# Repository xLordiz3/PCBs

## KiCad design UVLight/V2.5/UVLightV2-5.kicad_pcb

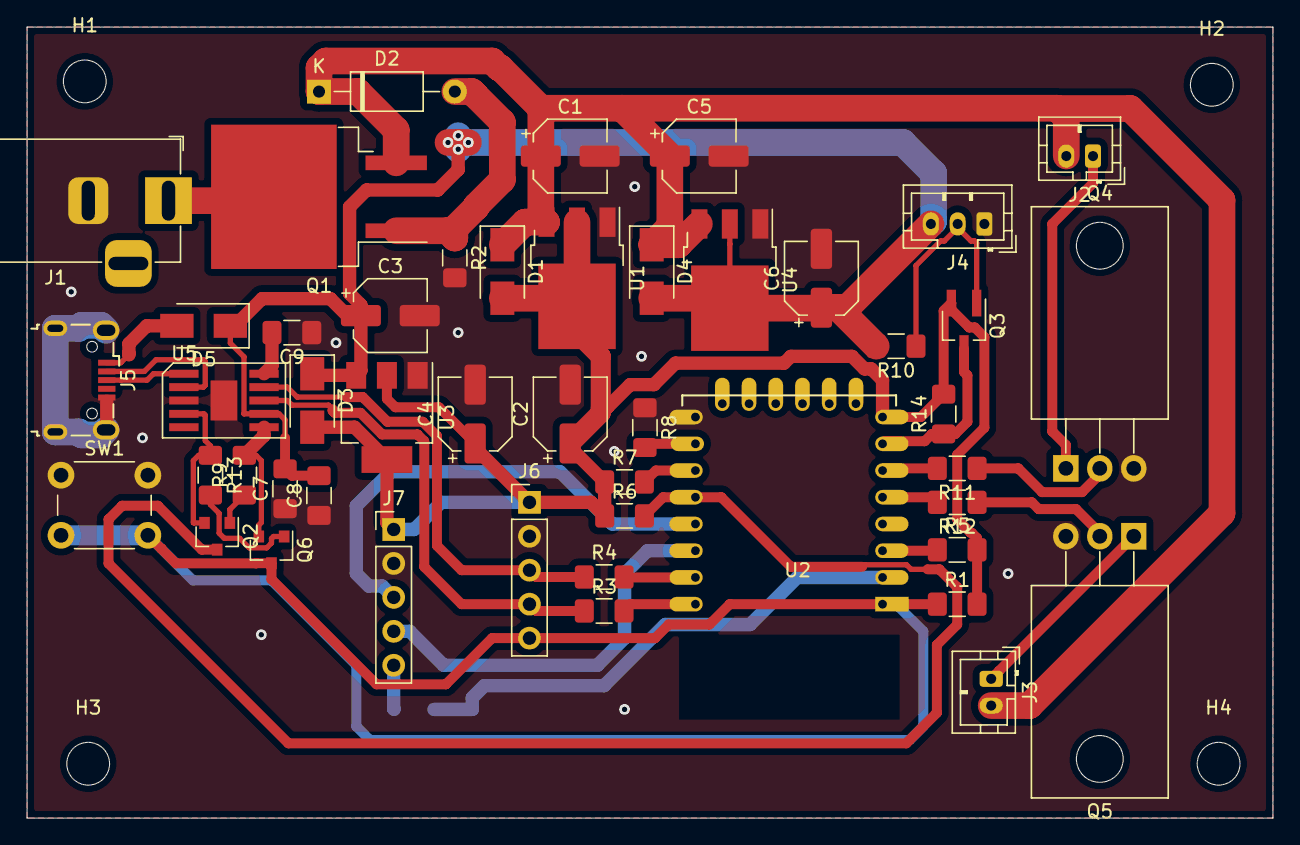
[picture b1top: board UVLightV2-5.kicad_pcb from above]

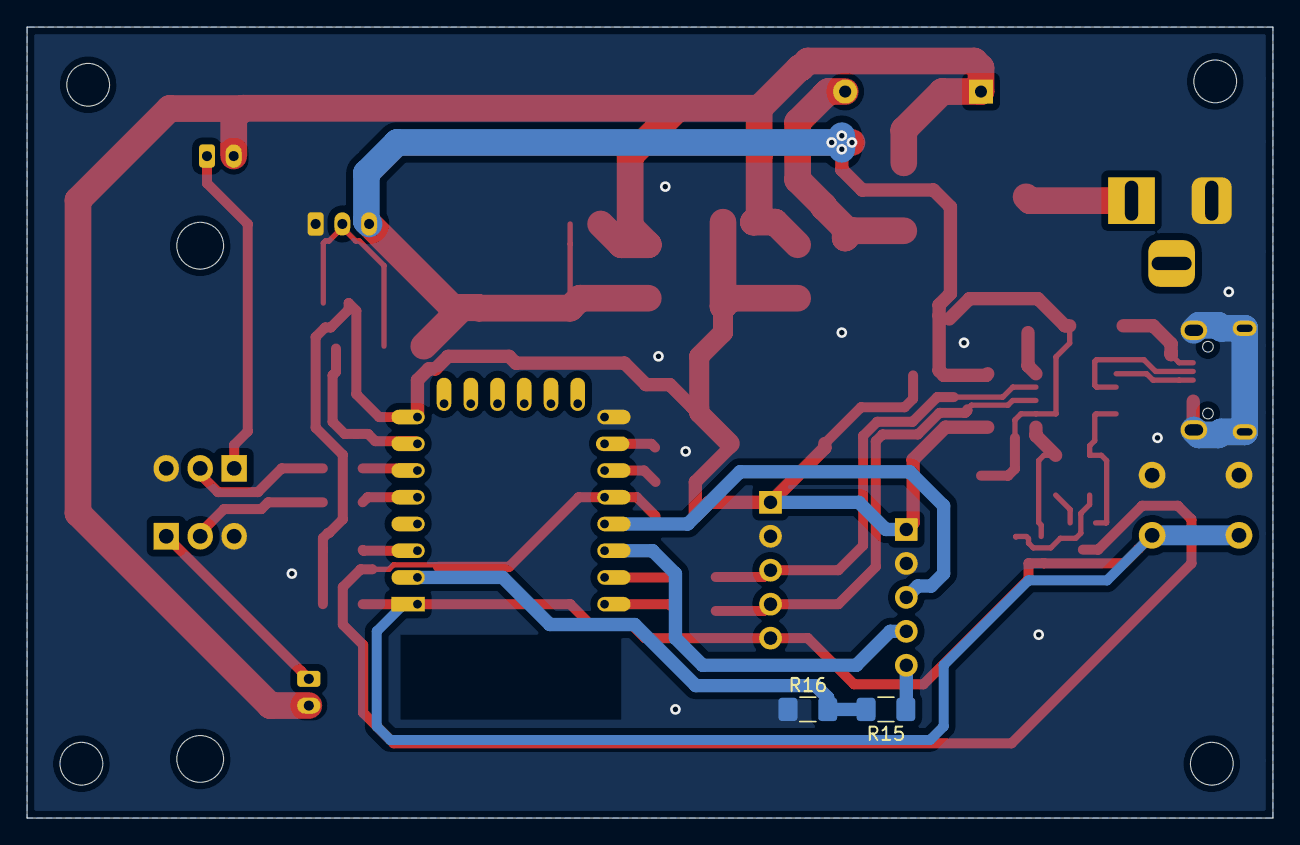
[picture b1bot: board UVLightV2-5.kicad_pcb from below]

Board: 2 copper layers, 93.2 x 59.2 mm, 53 parts (2 on the bottom side), 35 nets.

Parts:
C1, C2, C3, C4, C5, C6: C 10uF; CP_Elec_5x5.4
C7: C 10uF; C_1206_3216Metric_Pad1.42x1.75mm_HandSolder
C8, C9: C 100nF; C_1206_3216Metric_Pad1.42x1.75mm_HandSolder
D1, D3, D4, D5: 1N4002; D_SMA
D2: Z 9.1V; D_A-405_P10.16mm_Horizontal
H1, H2, H3, H4: MountingHole; MountingHole_3.2mm_M3
J1: Barrel_Jack_MountingPin; BarrelJack_Horizontal
J2: 24V LED Out; JST_PH_B2B-PH-K_1x02_P2.00mm_Vertical
J3: 24V Fan Out; JST_PH_B2B-PH-K_1x02_P2.00mm_Vertical
J4: 5V RGB Out; JST_PH_B3B-PH-K_1x03_P2.00mm_Vertical
J5: USB_B_Micro; USB_Micro-B_Wuerth_629105150521
J6: Alt Program; PinHeader_1x05_P2.54mm_Vertical
J7: Out IO; PinHeader_1x05_P2.54mm_Vertical
Q1: FQB47P06; TO-263-2
Q2, Q6: S8050; SOT-23
Q3: BS170; SOT-23W_Handsoldering
Q4, Q5: FQP30N06L; TO-220-3_Horizontal_TabDown
R1, R5, R6, R7, R8, R9, R13: R 10K; R_1206_3216Metric_Pad1.42x1.75mm_HandSolder
R2, R11, R12: R; R_1206_3216Metric_Pad1.42x1.75mm_HandSolder
R3, R4: R 470; R_1206_3216Metric_Pad1.42x1.75mm_HandSolder
R10, R14: R 4.7K; R_1206_3216Metric_Pad1.42x1.75mm_HandSolder
R15: R 220K; R_1206_3216Metric_Pad1.42x1.75mm_HandSolder
R16: R 100K; R_1206_3216Metric_Pad1.42x1.75mm_HandSolder
SW1: SW_Push; SW_PUSH_6mm
U1: IFX27001TFV33ATMA1; TO-252-3_TabPin2
U2: ESP-12E
U3: LM1117-3.3; SOT-223-3_TabPin2
U4: IFX27001TFV50ATMA1; TO-252-3_TabPin2
U5: ch340k; ESSOP-10

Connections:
+3.3VA: C2.1, C4.1, D1.2, D3.2, J6.1, J7.1, Q3.2, R1.2, R5.2, R6.1, R7.1, R14.2, U1.2, U2.8, U3.2
+5V: C3.1, C6.1, C7.2, C8.2, D3.1, D4.2, D5.1, J4.3, R10.2, U3.3, U4.2, U5.7
+24V: C1.1, C5.1, D1.1, D2.1, D4.1, J2.2, J3.2, Q1.3, U1.3, U4.3
/ADC: R15.2, R16.2, U2.2
/DTR: Q2.2, R13.1, U5.4
/Fan: R12.2, U2.5
/IO0: Q2.3, R6.2, U2.12
/IO4: J7.3, U2.13
/IO5: J7.4, U2.14
/RGB: Q3.3, R14.1, U2.7
/RST: J6.5, Q6.3, R1.1, SW1.2, U2.1
/RTS: Q6.2, R9.2, U5.6
/RX: J6.3, R4.1, U5.9
/TX: J6.4, R3.1, U5.8
/White: R11.2, U2.6
GND: C1.2, C2.2, C3.2, C4.2, C5.2, C6.2, C7.1, C8.1, C9.1, J1.2, J4.1, J5.5, J5.6, J6.2, J7.2, Q4.3, Q5.3, R2.2, R8.1, R16.1, SW1.1, U1.1, U2.9, U3.1, U4.1, U5.0, U5.3
unnamed: C9.2, U5.10
unnamed: D2.2, Q1.1, R2.1
unnamed: D5.2, J5.1
unnamed: J1.1, Q1.2
unnamed: J2.1, Q4.1
unnamed: J3.1, Q5.1
unnamed: J4.2, Q3.1, R10.1
unnamed: J5.2, U5.2
unnamed: J5.3, U5.1
unnamed: J7.5, R15.1
unnamed: Q2.1, R9.1
unnamed: Q4.2, R11.1
unnamed: Q5.2, R12.1
unnamed: Q6.1, R13.2
unnamed: R3.2, U2.16
unnamed: R4.2, U2.15
unnamed: R5.1, U2.3
unnamed: R7.2, U2.11
unnamed: R8.2, U2.10

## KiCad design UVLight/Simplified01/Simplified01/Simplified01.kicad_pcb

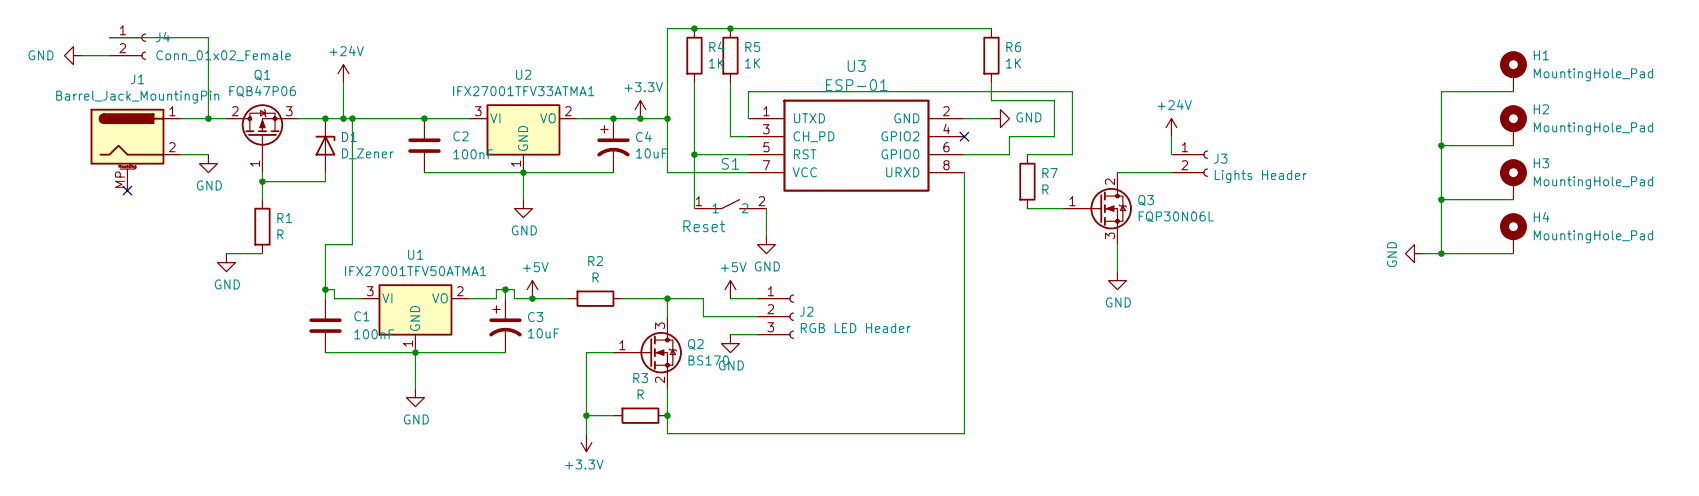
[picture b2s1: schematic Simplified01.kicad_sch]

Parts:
C1, C2: 100nF; C_1206_3216Metric_Pad1.33x1.80mm_HandSolder
C3, C4: 10uF; CP_Elec_5x5.4
D1: D_Zener; D_SOD-123F
H1, H2, H3, H4: MountingHole_Pad; MountingHole_2.2mm_M2_Pad
J1: Barrel_Jack_MountingPin; BarrelJack_Horizontal
J2: RGB LED Header; JST_XH_B3B-XH-A_1x03_P2.50mm_Vertical
J3: Lights Header; JST_XH_B2B-XH-A_1x02_P2.50mm_Vertical
J4: Conn_01x02_Female; JST_XH_B2B-XH-A_1x02_P2.50mm_Vertical
Q1: FQB47P06; TO-252-2
Q2: BS170; SOT-23
Q3: FQP30N06L; TO-220-3_Vertical
R1, R2, R3, R7: R; R_1206_3216Metric_Pad1.30x1.75mm_HandSolder
R4, R5, R6: 1K; R_1206_3216Metric_Pad1.30x1.75mm_HandSolder
S1: Reset; SW_SPST_EVQPE1
U1: IFX27001TFV50ATMA1; TO-252-3_TabPin2
U2: IFX27001TFV33ATMA1; TO-252-3_TabPin2
U3: ESP-01

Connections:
+3V3: C4.1, Q2.1 (G), R3.2, R4.1, R5.1, R6.1, U2.2 (VO), U3.7 (VCC)
+5V: C3.1, J2.1, R2.2, U1.2 (VO)
+24V: C1.1, C2.1, D1.1 (K), J3.1, Q1.3 (S), U1.3 (VI), U2.3 (VI)
GND: C1.2, C2.2, C3.2, C4.2, H1.1, H2.1, H3.1, H4.1, J1.2, J2.3, J4.2, Q3.3 (S), R1.2, S1.2, U1.1 (GND), U2.1 (GND), U3.2 (GND)
unnamed: D1.2 (A), Q1.1 (G), R1.1
unnamed: J1.1, J4.1, Q1.2 (D)
unnamed: J2.2, Q2.3 (D), R2.1
unnamed: J3.2, Q3.2 (D)
unnamed: Q2.2 (S), R3.1, U3.8 (URXD)
unnamed: Q3.1 (G), R7.2
unnamed: R4.2, S1.1, U3.5 (RST)
unnamed: R5.2, U3.3 (CH_PD)
unnamed: R6.2, U3.6 (GPIO0)
unnamed: R7.1, U3.1 (UTXD)

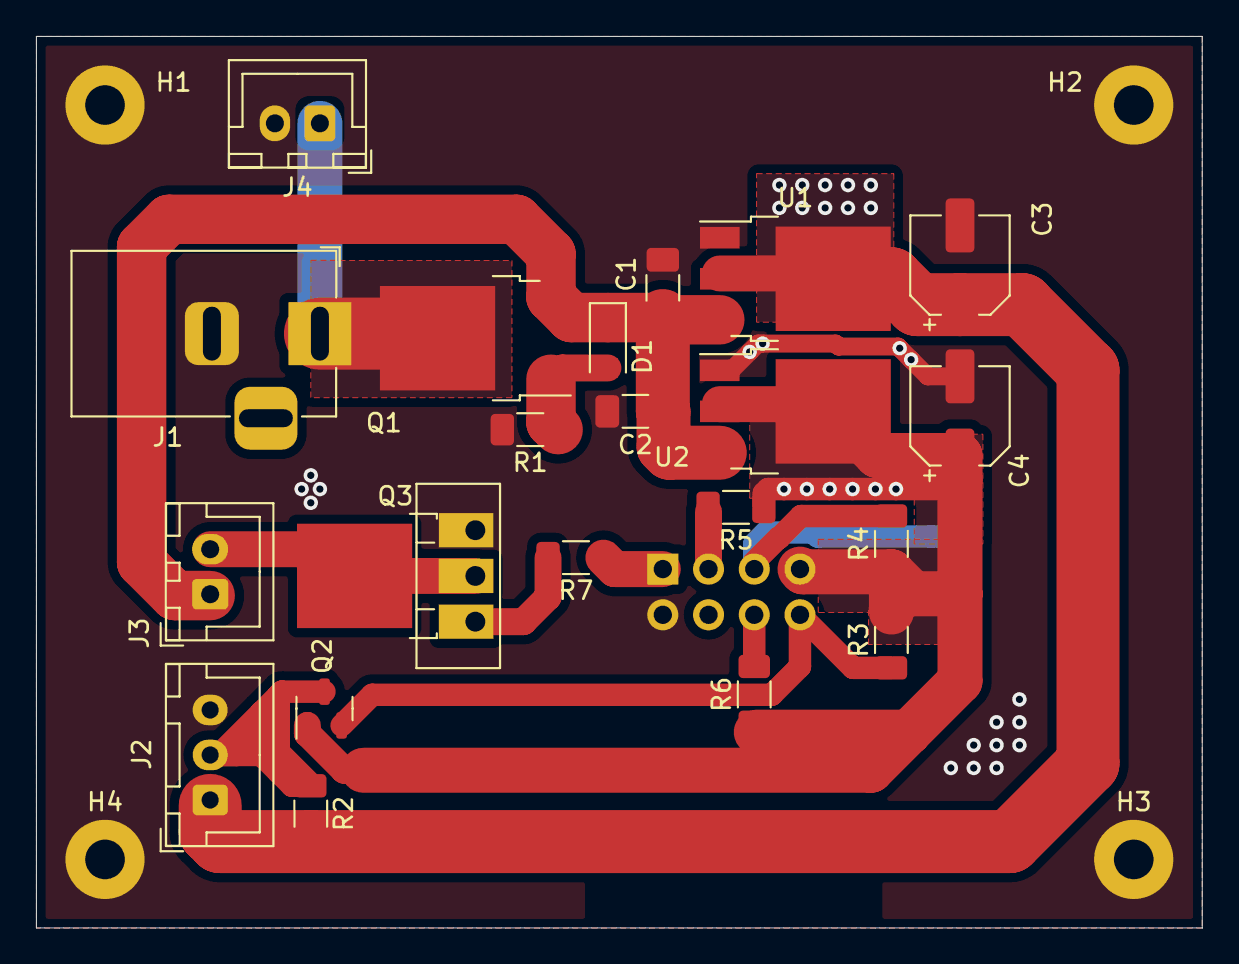
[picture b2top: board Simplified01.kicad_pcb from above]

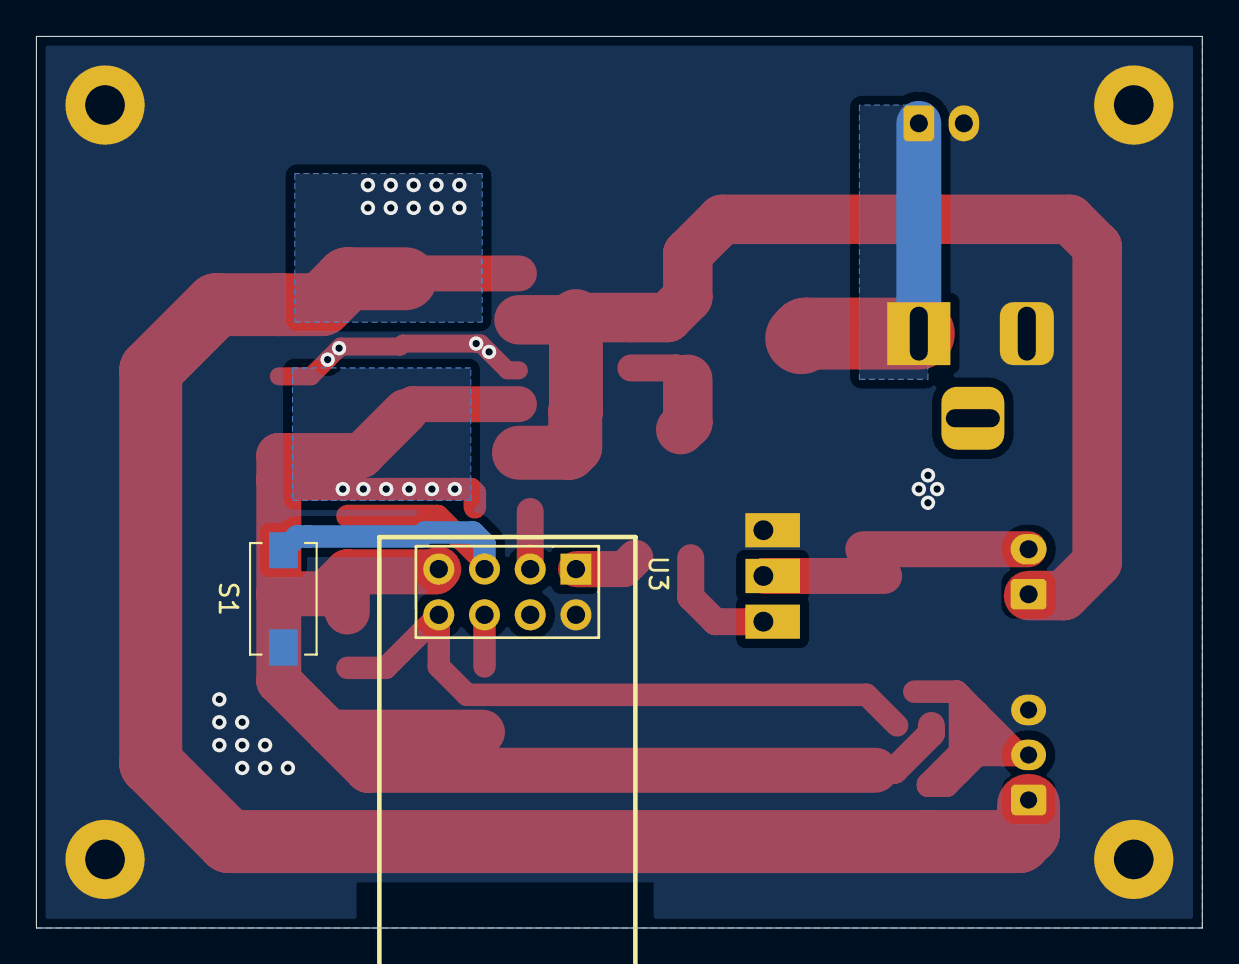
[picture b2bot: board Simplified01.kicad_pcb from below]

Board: 2 copper layers, 64.8 x 49.5 mm, 27 parts (2 on the bottom side), 14 nets.

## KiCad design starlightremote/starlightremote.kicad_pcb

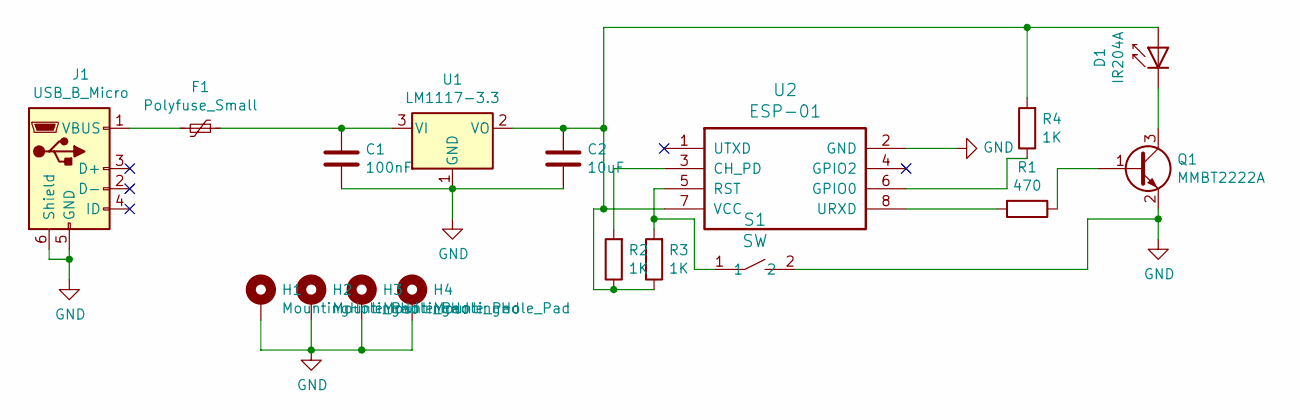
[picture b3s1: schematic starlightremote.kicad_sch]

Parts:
C1: 100nF; C_1206_3216Metric_Pad1.33x1.80mm_HandSolder
C2: 10uF; CP_Elec_5x5.4
D1: IR204A; LED_D3.0mm_IRBlack
F1: Polyfuse_Small; Fuse_0805_2012Metric_Pad1.15x1.40mm_HandSolder
H1, H2, H3, H4: MountingHole_Pad; MountingHole_2.2mm_M2_Pad
J1: USB_B_Micro; USB_Micro-B_Wuerth_629105150521
Q1: MMBT2222A; SOT-23
R1: 470; R_1206_3216Metric_Pad1.30x1.75mm_HandSolder
R2, R3, R4: 1K; R_1206_3216Metric_Pad1.30x1.75mm_HandSolder
S1: SW; SW_SPST_CK_RS282G05A3
U1: LM1117-3.3; SOT-223-3_TabPin2
U2: ESP-01

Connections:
GND: C1.2, C2.2, H1.1, H2.1, H3.1, H4.1, J1.5 (GND), J1.6 (Shield), Q1.2 (E), S1.2, U1.1 (GND), U2.2 (GND)
unnamed: C1.1, F1.1, U1.3 (VI)
unnamed: C2.1, D1.2 (A), R2.1, R3.1, R4.2, U1.2 (VO), U2.7 (VCC)
unnamed: D1.1 (K), Q1.3 (C)
unnamed: F1.2, J1.1 (VBUS)
unnamed: Q1.1 (B), R1.1
unnamed: R1.2, U2.8 (URXD)
unnamed: R2.2, U2.3 (CH_PD)
unnamed: R3.2, S1.1, U2.5 (RST)
unnamed: R4.1, U2.6 (GPIO0)

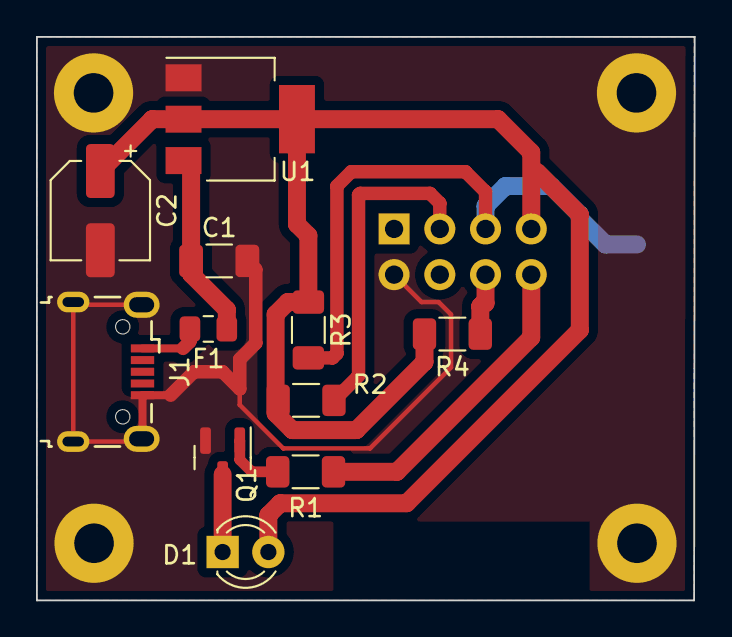
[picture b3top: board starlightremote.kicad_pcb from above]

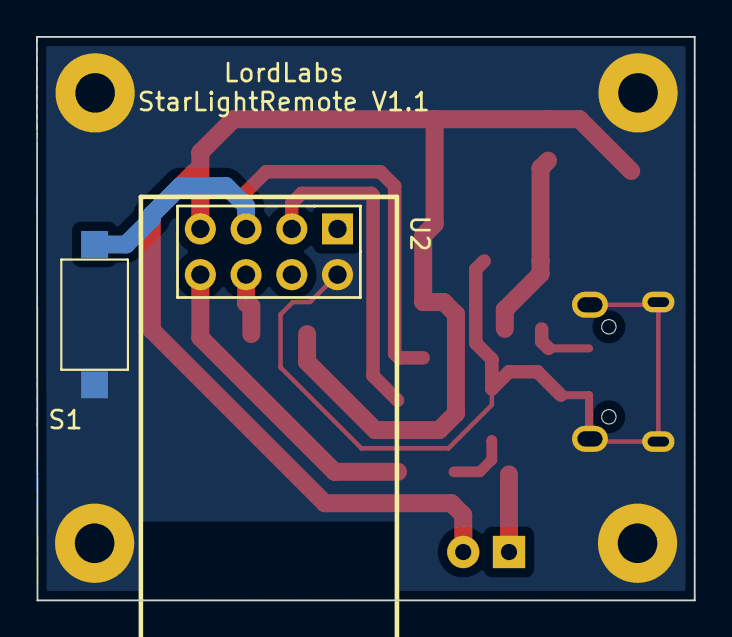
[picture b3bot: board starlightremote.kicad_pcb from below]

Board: 2 copper layers, 36.5 x 31.3 mm, 17 parts (2 on the bottom side), 10 nets.

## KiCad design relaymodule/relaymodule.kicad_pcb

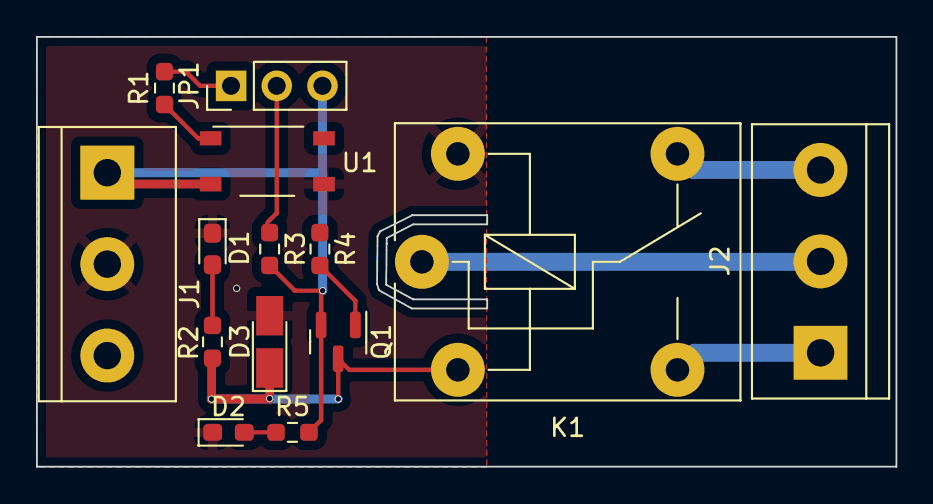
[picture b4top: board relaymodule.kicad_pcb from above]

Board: 2 copper layers, 47.8 x 23.9 mm, 14 parts (0 on the bottom side), 12 nets.

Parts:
D1, D2: LED; LED_0603_1608Metric_Pad1.05x0.95mm_HandSolder
D3: D; D_MicroMELF_Handsoldering
J1: Inputs; TerminalBlock_bornier-3_P5.08mm
J2: Outputs; TerminalBlock_bornier-3_P5.08mm
JP1: High/Low Jumper; PinHeader_1x03_P2.54mm_Vertical
K1: 12V Relay; Relay_SPDT_Finder_36.11
Q1: S8550; SOT-23
R1, R2, R3, R4, R5: R; R_0603_1608Metric_Pad0.98x0.95mm_HandSolder
U1: Octocupler; MFSOP6-4_4.4x3.6mm_P1.27mm

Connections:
GND: D1.1 (K), D2.1 (K), D3.2 (A), J1.2, K1.A2, U1.4
unnamed: J1.1, JP1.3 (B), Q1.2 (B), R3.2, R5.2, U1.3
unnamed: J2.2, K1.11
unnamed: JP1.1 (A), R1.2
unnamed: JP1.2 (C), R3.1
unnamed: J2.3, K1.12
unnamed: J2.1, K1.14
unnamed: Q1.1 (E), R4.2
unnamed: D3.1 (K), K1.A1, Q1.3 (C), R2.1
unnamed: R1.1, U1.1
unnamed: D1.2 (A), R2.2
unnamed: D2.2 (A), R5.1

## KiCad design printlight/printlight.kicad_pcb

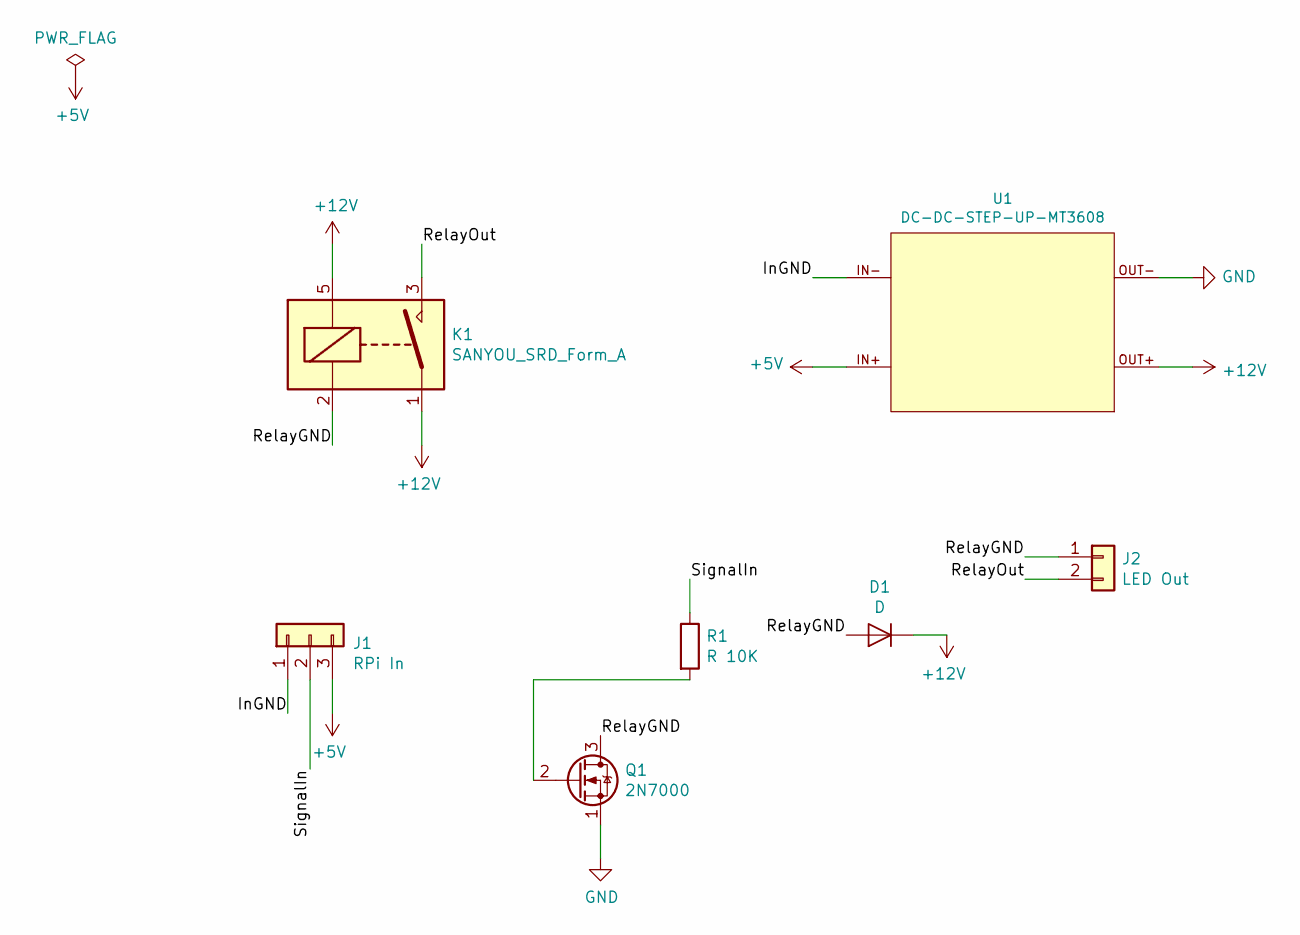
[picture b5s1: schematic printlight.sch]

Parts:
D1: D; D_DO-34_SOD68_P7.62mm_Horizontal
J1: RPi In; PinSocket_1x03_P2.54mm_Vertical
J2: LED Out; JST_XH_B2B-XH-A_1x02_P2.50mm_Vertical
K1: SANYOU_SRD_Form_A; Relay_SPST_SANYOU_SRD_Series_Form_A
Q1: 2N7000; TO-92_Inline
R1: R 10K; R_Axial_DIN0204_L3.6mm_D1.6mm_P7.62mm_Horizontal
U1: DC-DC-STEP-UP-MT3608

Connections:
+5V: J1.3, U1.IN+
+12V: D1.1 (K), K1.1, K1.5, U1.OUT+
/InGND: J1.1, U1.IN-
/RelayGND: D1.2 (A), J2.1, K1.2, Q1.3 (D)
/RelayOut: J2.2, K1.3
/SignalIn: J1.2, R1.1
GND: Q1.1 (S), U1.OUT-
unnamed: Q1.2 (G), R1.2

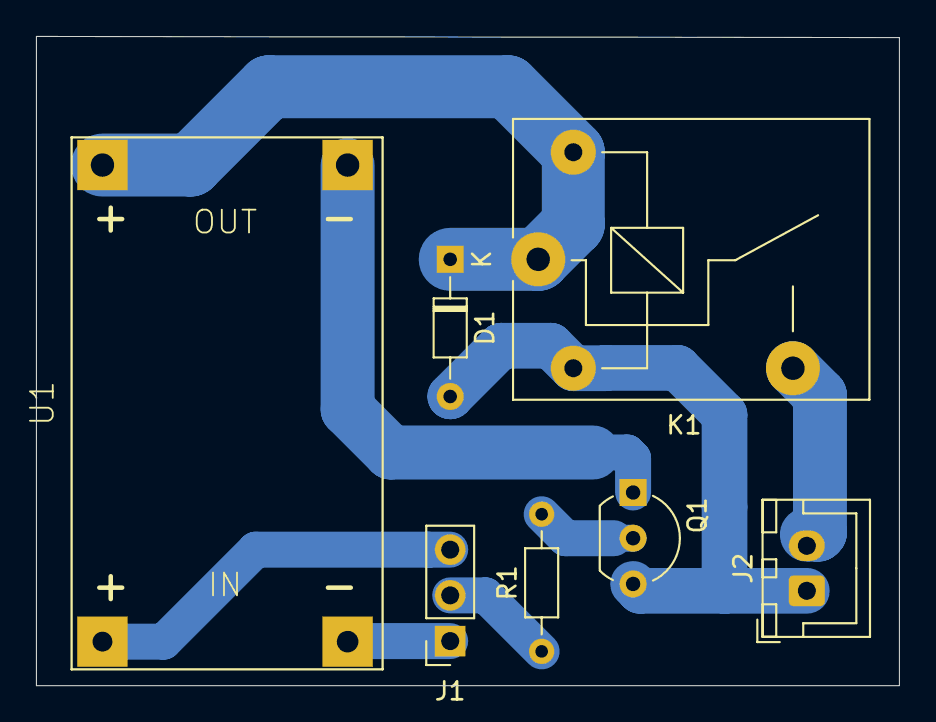
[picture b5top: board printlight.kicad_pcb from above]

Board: 2 copper layers, 47.9 x 36.1 mm, 7 parts (0 on the bottom side), 8 nets.

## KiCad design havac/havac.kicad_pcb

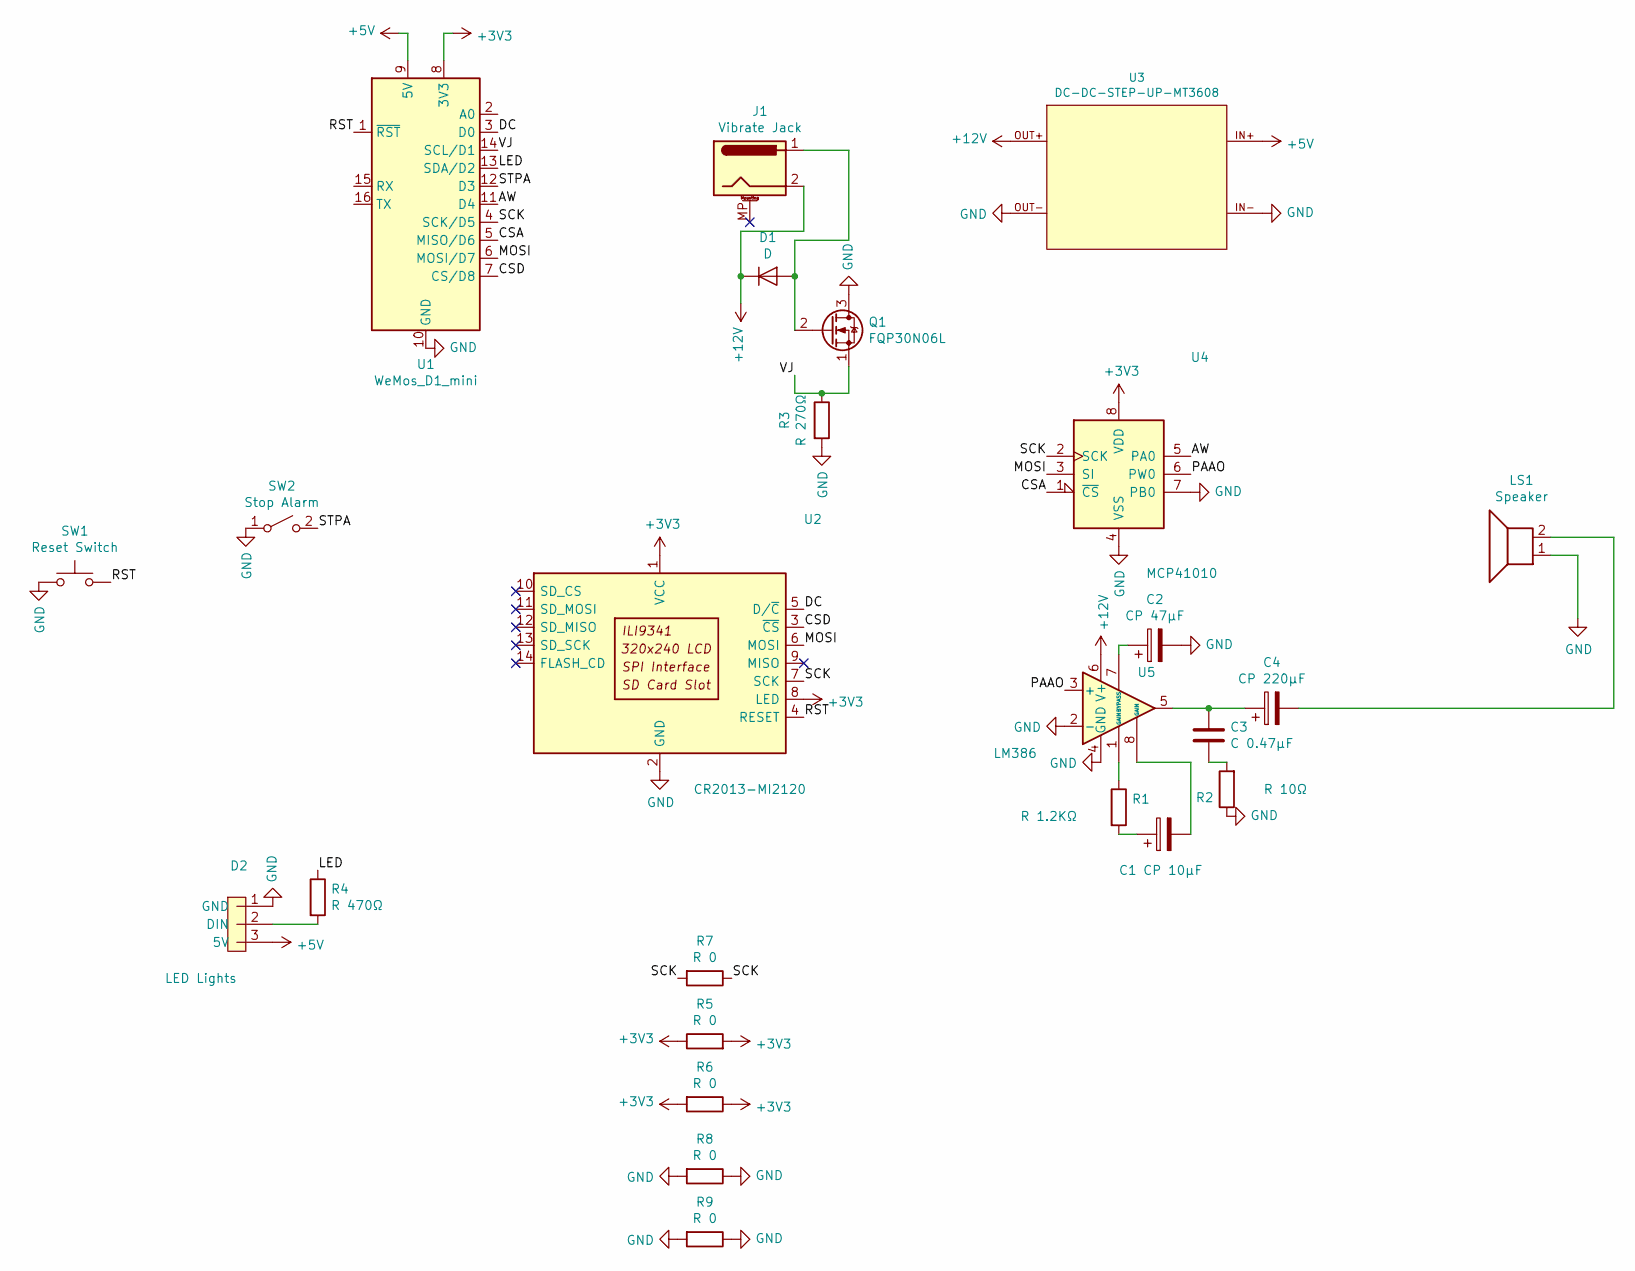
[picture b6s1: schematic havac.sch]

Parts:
C1: CP 10μF; CP_Radial_D4.0mm_P1.50mm
C2: CP 47μF; CP_Radial_D4.0mm_P1.50mm
C3: C 0.47μF; C_1206_3216Metric_Pad1.42x1.75mm_HandSolder
C4: CP 220μF; CP_Radial_D4.0mm_P1.50mm
D1: D; D_MELF-RM10_Universal_Handsoldering
D2: LED Lights; 3pin-rgbled-connector
J1: Vibrate Jack; BarrelJack_Horizontal
LS1: Speaker; PinHeader_1x02_P2.54mm_Vertical
Q1: FQP30N06L; TO-220-3_Vertical
R1: R 1.2KΩ; R_1206_3216Metric_Pad1.42x1.75mm_HandSolder
R2: R 10Ω; R_1206_3216Metric_Pad1.42x1.75mm_HandSolder
R3: R 270Ω; R_1206_3216Metric_Pad1.42x1.75mm_HandSolder
R4: R 470Ω; R_1206_3216Metric_Pad1.42x1.75mm_HandSolder
R5, R6, R7, R8, R9: R 0; R_1206_3216Metric_Pad1.42x1.75mm_HandSolder
SW1: Reset Switch; SW_DIP_SPSTx01_Slide_6.7x4.1mm_W7.62mm_P2.54mm_LowProfile
SW2: Stop Alarm; SW_DIP_SPSTx01_Slide_6.7x4.1mm_W7.62mm_P2.54mm_LowProfile
U1: WeMos_D1_mini; WEMOS_D1_mini_light
U2: CR2013-MI2120
U3: DC-DC-STEP-UP-MT3608
U4: MCP41010; DIP-8_W7.62mm_LongPads
U5: LM386; DIP-8_W7.62mm_LongPads

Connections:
+3V3: R5.1, R5.2, R6.1, R6.2, U1.8 (3V3), U2.1 (VCC), U2.8 (LED), U4.8 (VDD)
+5V: D2.3 (5V), U1.9 (5V), U3.IN+
+12V: D1.1 (K), J1.2, U3.OUT+, U5.6 (V+)
/AW: U1.11 (D4), U4.5 (PA0)
/CSA: U1.5 (MISO/D6), U4.1 (~CS)
/CSD: U1.7 (CS/D8), U2.3 (~CS)
/DC: U1.3 (D0), U2.5 (D/~C)
/LED: R4.1, U1.13 (SDA/D2)
/MOSI: U1.6 (MOSI/D7), U2.6 (MOSI), U4.3 (SI)
/PAAO: U4.6 (PW0), U5.3 (+)
/RST: SW1.2, U1.1 (~RST), U2.4 (RESET)
/SCK: R7.1, R7.2, U1.4 (SCK/D5), U2.7 (SCK), U4.2 (SCK)
/STPA: SW2.2 (B), U1.12 (D3)
/VJ: Q1.1 (S), R3.1, U1.14 (SCL/D1)
GND: C2.2, D2.1 (GND), LS1.1, Q1.3 (D), R2.1, R3.2, R8.1, R8.2, R9.1, R9.2, SW1.1, SW2.1 (A), U1.10 (GND), U2.2 (GND), U3.IN-, U3.OUT-, U4.4 (VSS), U4.7 (PB0), U5.2 (-), U5.4 (GND)
unnamed: C1.1, R1.2
unnamed: C1.2, U5.8 (GAIN)
unnamed: C2.1, U5.7 (BYPASS)
unnamed: C3.1, C4.1, U5.5
unnamed: C3.2, R2.2
unnamed: C4.2, LS1.2
unnamed: D1.2 (A), J1.1, Q1.2 (G)
unnamed: D2.2 (DIN), R4.2
unnamed: R1.1, U5.1 (GAIN)

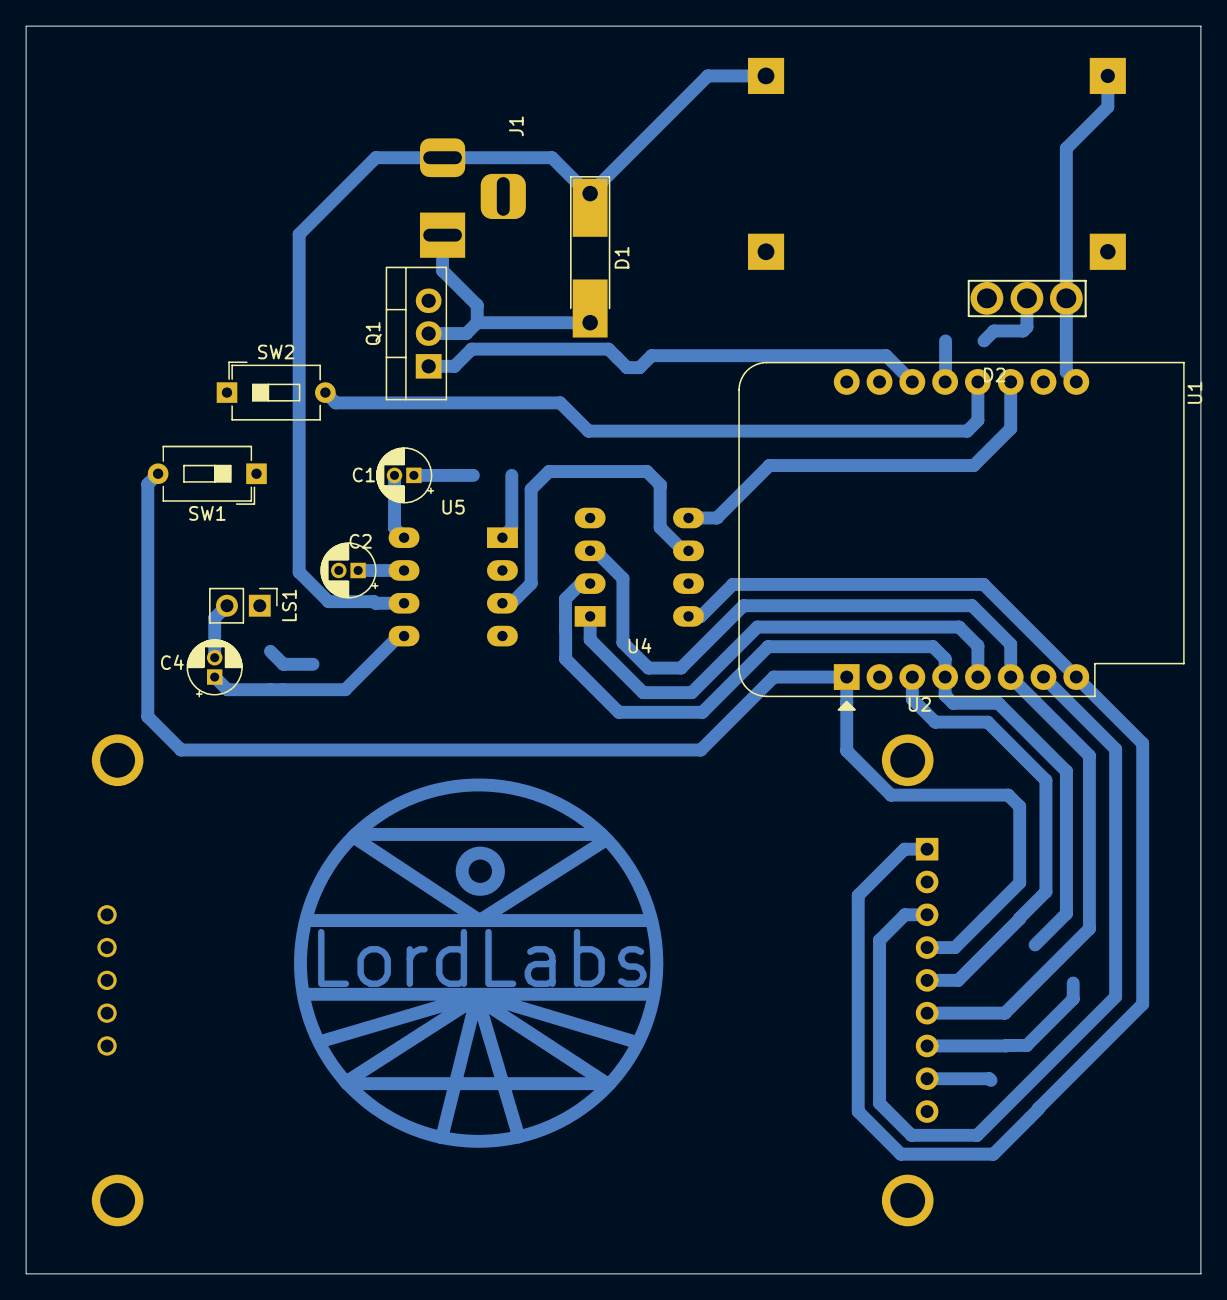
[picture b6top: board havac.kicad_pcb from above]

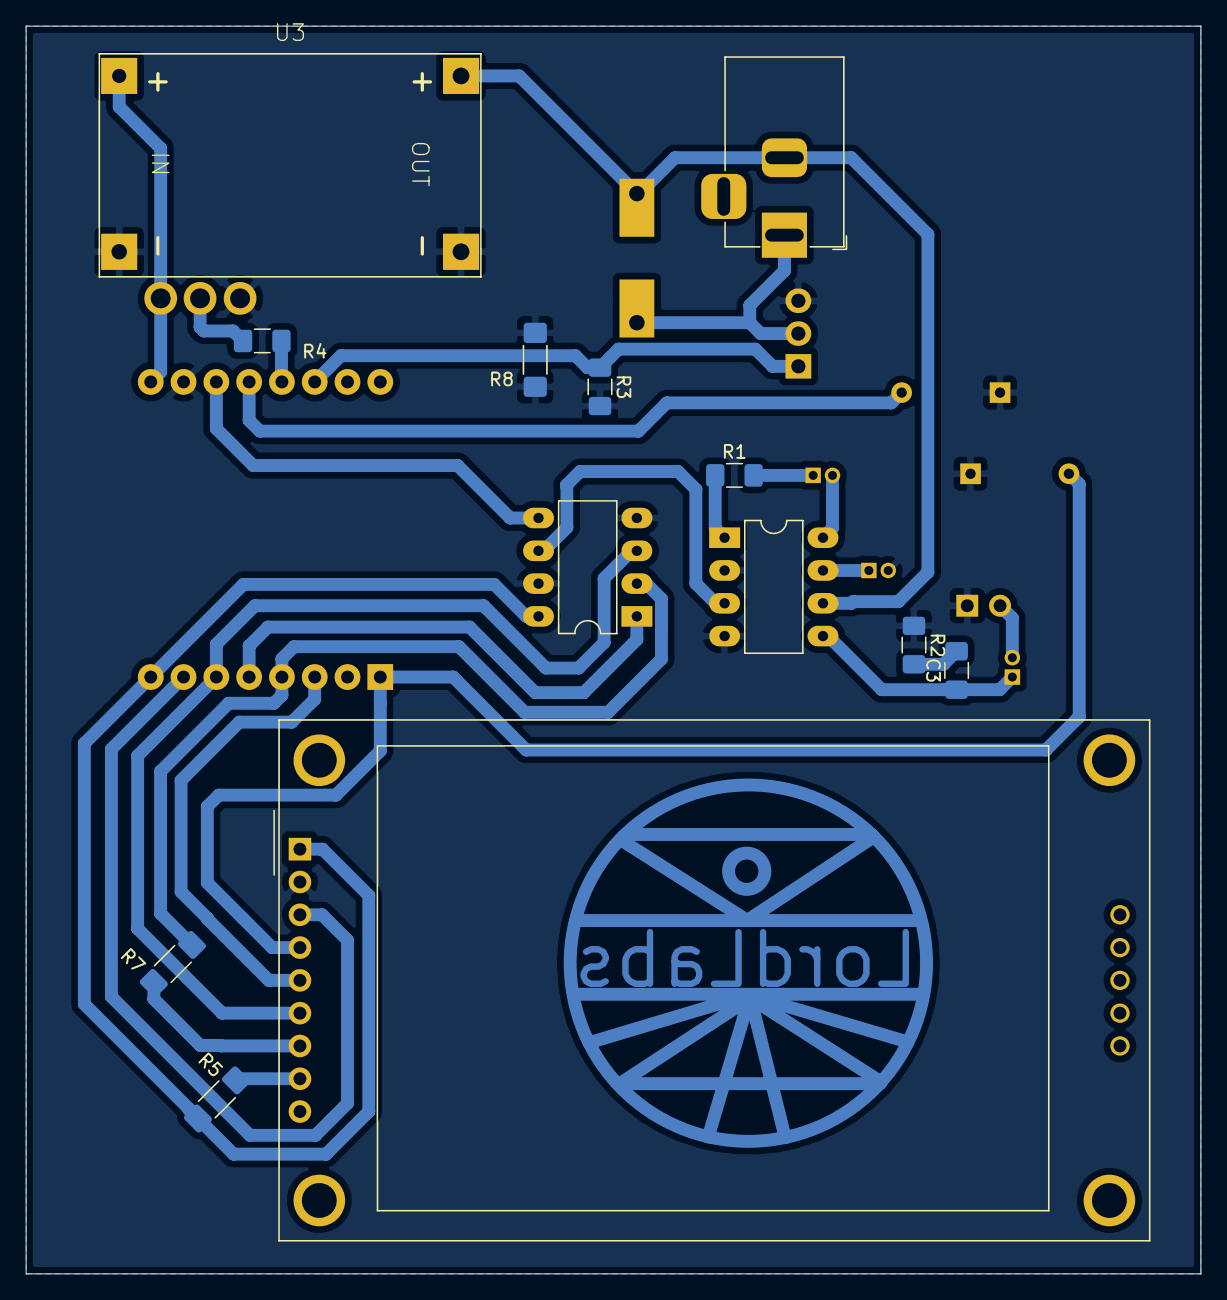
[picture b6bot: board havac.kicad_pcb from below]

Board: 2 copper layers, 91.0 x 96.6 mm, 23 parts (13 on the bottom side), 24 nets.
